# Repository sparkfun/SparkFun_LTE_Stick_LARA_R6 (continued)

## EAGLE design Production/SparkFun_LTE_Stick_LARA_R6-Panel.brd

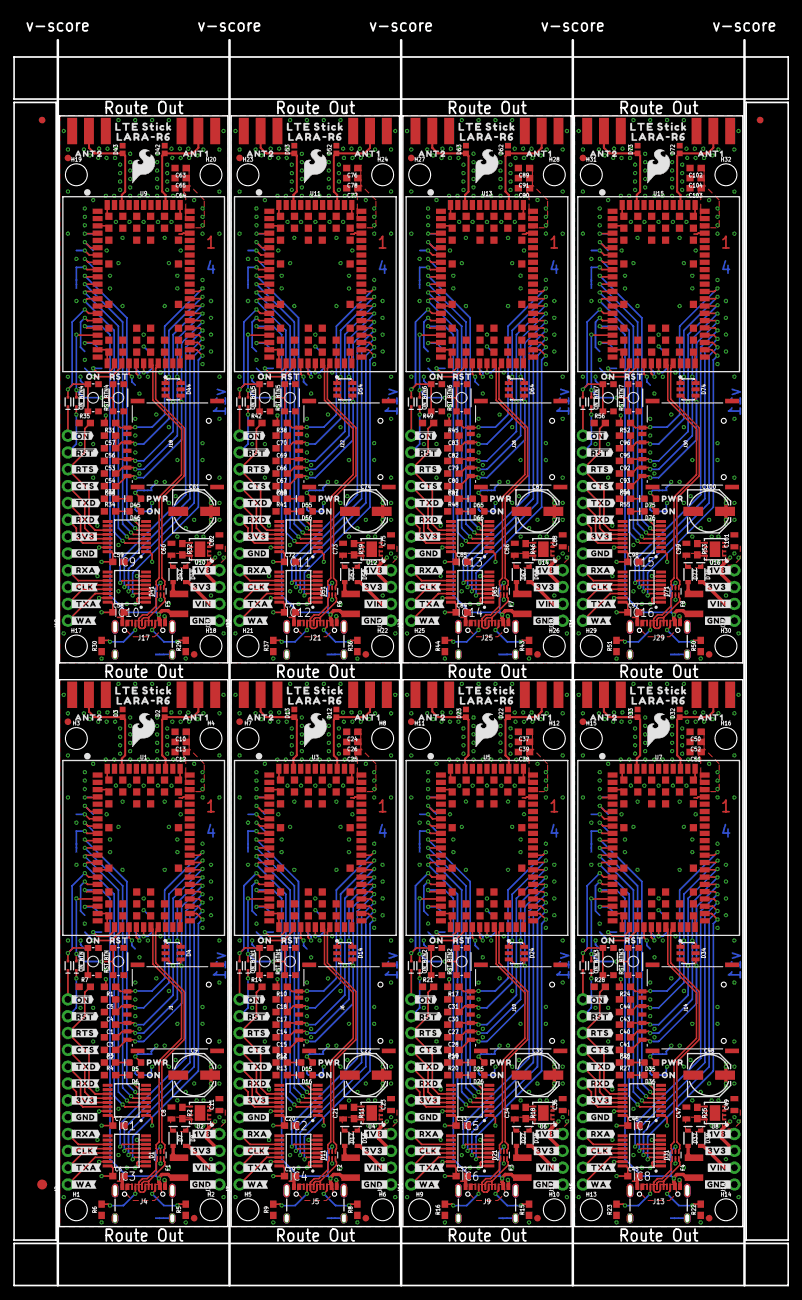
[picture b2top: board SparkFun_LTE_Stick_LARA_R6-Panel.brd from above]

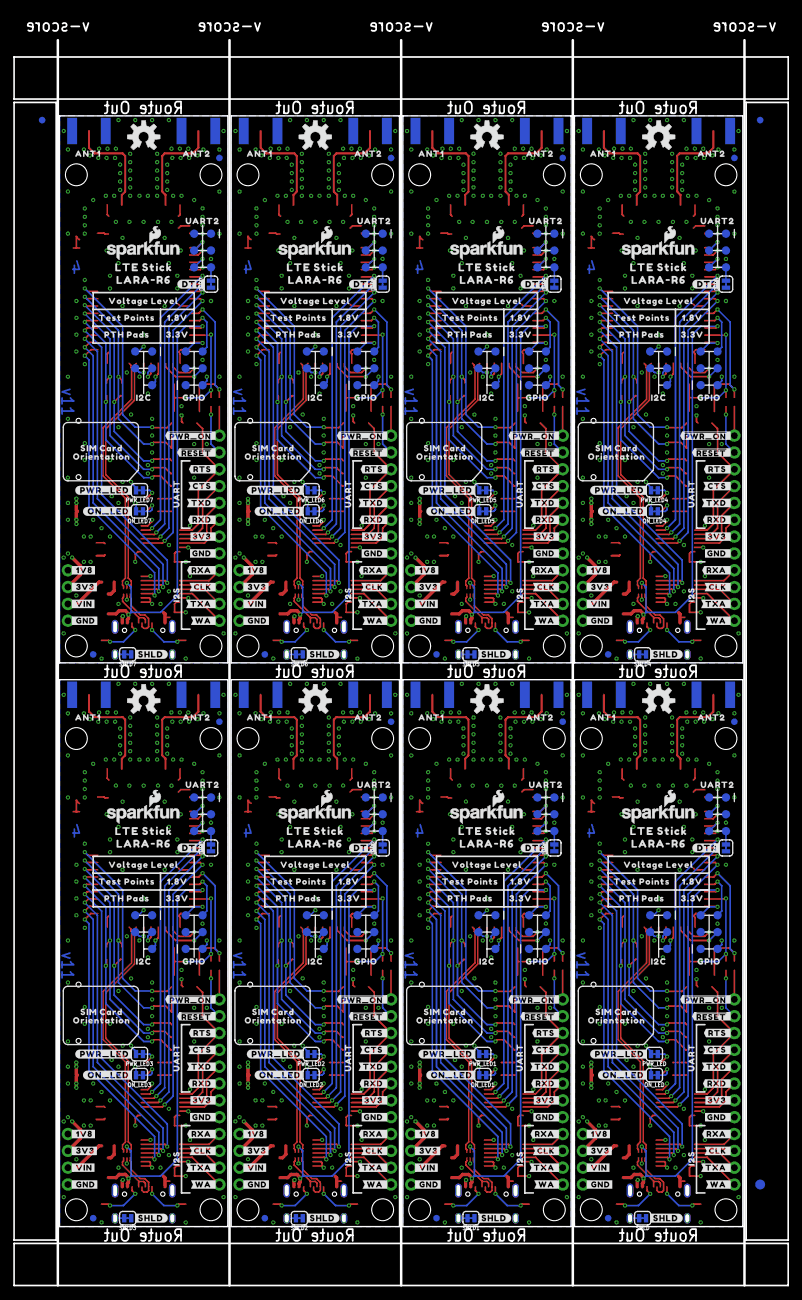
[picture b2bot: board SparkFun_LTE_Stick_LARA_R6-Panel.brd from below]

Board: 4 copper layers, 116.8 x 188.0 mm, 1086 parts (491 on the bottom side), 456 nets.

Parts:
C1, C2, C3, C4, C14, C15, C16, C17, C27, C28, C29, C30, C40, C41, C42, C43, C53, C54, C55, C56, C66, C67, C68, C69, C79, C80, C81, C82, C92, C93, C94, C95: 47pF; 0603
C5, C6, C7, C10, C18, C19, C20, C24, C31, C32, C33, C37, C44, C45, C46, C50, C57, C58, C59, C63, C70, C71, C72, C76, C83, C84, C85, C89, C96, C97, C98, C102: 0.1uF; 0603
C8, C11, C21, C23, C34, C36, C47, C49, C60, C62, C73, C75, C86, C88, C99, C101: 10uF; 0805
C9, C22, C35, C48, C61, C74, C87, C100: 100uF; PANASONIC_D
C12, C25, C38, C51, C64, C77, C90, C103: 15pF; 0603
C13, C26, C39, C52, C65, C78, C91, C104: 68pF; 0603
D1, D11, D21, D31, D41, D51, D61, D71: PRTR5V0U2F; SOT886
D2, D3, D12, D13, D22, D23, D32, D33, D42, D43, D52, D53, D62, D63, D72, D73: PESD0402-0402; 0402
D4, D14, D24, D34, D44, D54, D64, D74: DT1042-04SO-7; SOT23-6L
D5, D6, D15, D16, D25, D26, D35, D36, D45, D46, D55, D56, D65, D66, D75, D76: Red; LED-0603
D7, D8, D17, D18, D27, D28, D37, D38, D47, D48, D57, D58, D67, D68, D77, D78: 3A/10V/280mV; SOD-323
D9, D10, D19, D20, D29, D30, D39, D40, D49, D50, D59, D60, D69, D70, D79, D80: 120mA/40V/370mV; SOD-523
DTR, DTR1, DTR2, DTR3, DTR4, DTR5, DTR6, DTR7: JUMPER-SMT_2_NC_TRACE_SILK; SMT-JUMPER_2_NC_TRACE_SILK
E1, E2, E3, E4, E5, E6, E7, E8, E9, E10, E11, E12, E13, E14, E15, E16: ANTENNA-SMA-GROUNDEDEDGE_SMA; SMA-EDGE
E$1, E$2, E$3, E$4: FIDUCIAL-1X2
E$5, E$6: FIDUCIAL-1.5X3
F1, F2, F3, F4, F5, F6, F7, F8: 6V/2A; 1210
FD1, FD2, FD3, FD4, FD5, FD6, FD7, FD8, FD9, FD10, FD11, FD12, FD13, FD14, FD15, FD16, FD17, FD18, FD19, FD20, FD21, FD22, FD23, FD24, FD25, FD26, FD27, FD28, FD29, FD30, FD31, FD32: FIDUCIAL1X2; FIDUCIAL-1X2
H1, H2, H3, H4, H5, H6, H7, H8, H9, H10, H11, H12, H13, H14, H15, H16, H17, H18, H19, H20, H21, H22, H23, H24, H25, H26, H27, H28, H29, H30, H31, H32: STAND-OFF
IC1, IC2, IC3, IC4, IC5, IC6, IC7, IC8, IC9, IC10, IC11, IC12, IC13, IC14, IC15, IC16: SN74AVC4T774PW; SOP65P640X120-16N
J1, J6, J10, J14, J18, J22, J26, J30: NANO_SIM; NANO_SIM_PP
J2, J7, J11, J15, J19, J23, J27, J31: 1X12_NO_SILK
J3, J8, J12, J16, J20, J24, J28, J32: 1X04_NO_SILK
J4, J5, J9, J13, J17, J21, J25, J29: USB-C-16P_4LAYER-PADS
LOGO1, LOGO3, LOGO5, LOGO7, LOGO9, LOGO11, LOGO13, LOGO15: SFE_LOGO_NAME_FLAME.1_INCH; SFE_LOGO_NAME_FLAME_.1
LOGO2, LOGO4, LOGO6, LOGO8, LOGO10, LOGO12, LOGO14, LOGO16: OSHW-LOGOM; OSHW-LOGO-M
ON_BTN, ON_BTN1, ON_BTN2, ON_BTN3, ON_BTN4, ON_BTN5, ON_BTN6, ON_BTN7: MOMENTARY-SWITCH-SPST-SMD-4.6X2.8MM; TACTILE_SWITCH_SMD_4.6X2.8MM
ON_LED, ON_LED1, ON_LED2, ON_LED3, ON_LED4, ON_LED5, ON_LED6, ON_LED7: JUMPER-SMT_2_NC_TRACE_SILK; SMT-JUMPER_2_NC_TRACE_SILK
PWR_LED, PWR_LED1, PWR_LED2, PWR_LED3, PWR_LED4, PWR_LED5, PWR_LED6, PWR_LED7: JUMPER-SMT_2_NC_TRACE_SILK; SMT-JUMPER_2_NC_TRACE_SILK
R1, R2, R7, R10, R11, R14, R17, R18, R21, R24, R25, R28, R31, R32, R35, R38, R39, R42, R45, R46, R49, R52, R53, R56: 100k; 0603
R3, R12, R19, R26, R33, R40, R47, R54: 4.7k; 0603
R4, R13, R20, R27, R34, R41, R48, R55: 220; 0603
R5, R6, R8, R9, R15, R16, R22, R23, R29, R30, R36, R37, R43, R44, R50, R51: 5.1k; 0603
RST_BTN, RST_BTN1, RST_BTN2, RST_BTN3, RST_BTN4, RST_BTN5, RST_BTN6, RST_BTN7: MOMENTARY-SWITCH-SPST-SMD-4.6X2.8MM; TACTILE_SWITCH_SMD_4.6X2.8MM
SHLD, SHLD1, SHLD2, SHLD3, SHLD4, SHLD5, SHLD6, SHLD7: JUMPER-SMT_2_NC_TRACE_SILK; SMT-JUMPER_2_NC_TRACE_SILK
TP1, TP2, TP3, TP4, TP5, TP6, TP7, TP8, TP9, TP10, TP11, TP12, TP13, TP14, TP15, TP16, TP17, TP18, TP19, TP20, TP21, TP22, TP23, TP24, TP25, TP26, TP27, TP28, TP29, TP30, TP31, TP32, TP33, TP34, TP35, TP36, TP37, TP38, TP39, TP40, TP41, TP42, TP43, TP44, TP45, TP46, TP47, TP48, TP49, TP50, TP51, TP52, TP53, TP54, TP55, TP56, TP57, TP58, TP59, TP60, TP61, TP62, TP63, TP64, TP65, TP66, TP67, TP68, TP69, TP70, TP71, TP72, TP73, TP74, TP75, TP76, TP77, TP78, TP79, TP80, TP81, TP82, TP83, TP84, TP85, TP86, TP87, TP88, TP89, TP90, TP91, TP92, TP93, TP94, TP95, TP96, TP97, TP98, TP99, TP100, TP101, TP102, TP103, TP104, TP105, TP106, TP107, TP108, TP109, TP110, TP111, TP112, TP113, TP114, TP115, TP116, TP117, TP118, TP119, TP120, TP121, TP122, TP123, TP124, TP125, TP126, TP127, TP128, TP129, TP130, TP131, TP132, TP133, TP134, TP135, TP136: TEST-POINT3X5; PAD.03X.05
U1, U3, U5, U7, U9, U11, U13, U15: LARA-R6401; LARA-LGA
U2, U4, U6, U8, U10, U12, U14, U16: AP7361C-33; UDFN-8
U$1, U$25, U$55, U$79, U$123, U$140, U$184, U$201, U$245, U$262, U$306, U$323, U$367, U$384, U$428, U$445: LTE_STICK0
U$2, U$84, U$145, U$206, U$267, U$328, U$389, U$450: SFE_LOGO_FLAME_.2
U$3, U$15, U$63, U$73, U$124, U$134, U$185, U$195, U$246, U$256, U$307, U$317, U$368, U$378, U$429, U$439: #_3V3#0
U$4, U$5, U$64, U$65, U$125, U$126, U$186, U$187, U$247, U$248, U$308, U$309, U$369, U$370, U$430, U$431: #_GND#0
U$6, U$80, U$141, U$202, U$263, U$324, U$385, U$446: #SHLD#0
U$7, U$8, U$66, U$67, U$127, U$128, U$188, U$189, U$249, U$250, U$310, U$311, U$371, U$372, U$432, U$433: #GND_#0
U$9, U$12, U$68, U$70, U$129, U$131, U$190, U$192, U$251, U$253, U$312, U$314, U$373, U$375, U$434, U$436: #3V3_#0
U$10, U$81, U$142, U$203, U$264, U$325, U$386, U$447: #DTR#0
U$11, U$69, U$130, U$191, U$252, U$313, U$374, U$435: #VIN_#0
U$13, U$71, U$132, U$193, U$254, U$315, U$376, U$437: #1V8_#0
U$14, U$72, U$133, U$194, U$255, U$316, U$377, U$438: #_1V8#0
U$16, U$74, U$135, U$196, U$257, U$318, U$379, U$440: #_VIN#0
U$17, U$75, U$136, U$197, U$258, U$319, U$380, U$441: #_CTS#0
U$18, U$76, U$137, U$198, U$259, U$320, U$381, U$442: #_RTS#0
U$19, U$95, U$156, U$217, U$278, U$339, U$400, U$461: #RXD_#0
U$20, U$96, U$157, U$218, U$279, U$340, U$401, U$462: #TXD_#0
U$21, U$77, U$138, U$199, U$260, U$321, U$382, U$443: #_CLK#0
U$22, U$78, U$139, U$200, U$261, U$322, U$383, U$444: #_WA#0
U$23, U$97, U$158, U$219, U$280, U$341, U$402, U$463: #RXA_#0
U$24, U$98, U$159, U$220, U$281, U$342, U$403, U$464: #TXA_#0
U$26, U$105, U$166, U$227, U$288, U$349, U$410, U$471: SIM_CARD0
U$27, U$106, U$167, U$228, U$289, U$350, U$411, U$472: VOLTAGE_LEVEL0
U$28, U$82, U$143, U$204, U$265, U$326, U$387, U$448: PWR0
U$29, U$36, U$119, U$120, U$180, U$181, U$241, U$242, U$302, U$303, U$363, U$364, U$424, U$425, U$485, U$486: ANT10
U$30, U$107, U$168, U$229, U$290, U$351, U$412, U$473: TEST_POINTS0
U$31, U$35, U$85, U$86, U$146, U$147, U$207, U$208, U$268, U$269, U$329, U$330, U$390, U$391, U$451, U$452: LARA#R60
U$32, U$91, U$152, U$213, U$274, U$335, U$396, U$457: #_RXA#0
U$33, U$83, U$144, U$205, U$266, U$327, U$388, U$449: #_#RST##0
U$34, U$108, U$169, U$230, U$291, U$352, U$413, U$474: PTH_PADS0
U$37, U$39, U$115, U$116, U$176, U$177, U$237, U$238, U$298, U$299, U$359, U$360, U$420, U$421, U$481, U$482: ON0
U$38, U$90, U$151, U$212, U$273, U$334, U$395, U$456: ##PWR_ON#_#0
U$40, U$92, U$153, U$214, U$275, U$336, U$397, U$458: #_TXA#0
U$41, U$93, U$154, U$215, U$276, U$337, U$398, U$459: #_TXD#0
U$42, U$94, U$155, U$216, U$277, U$338, U$399, U$460: #_RXD#0
U$43, U$99, U$160, U$221, U$282, U$343, U$404, U$465: #CLK_#0
U$44, U$100, U$161, U$222, U$283, U$344, U$405, U$466: #WA_#0
U$45, U$87, U$148, U$209, U$270, U$331, U$392, U$453: #RTS_#0
U$46, U$88, U$149, U$210, U$271, U$332, U$393, U$454: #CTS_#0
U$47, U$89, U$150, U$211, U$272, U$333, U$394, U$455: ##RESET#_#0
U$48, U$101, U$162, U$223, U$284, U$345, U$406, U$467: UART0
U$49, U$102, U$163, U$224, U$285, U$346, U$407, U$468: I2S0
U$50, U$109, U$170, U$231, U$292, U$353, U$414, U$475: 1#8V0
U$51, U$103, U$164, U$225, U$286, U$347, U$408, U$469: ORIENTATION0
U$52, U$104, U$165, U$226, U$287, U$348, U$409, U$470: RST0
U$53, U$117, U$178, U$239, U$300, U$361, U$422, U$483: #ON_LED#0
U$54, U$110, U$171, U$232, U$293, U$354, U$415, U$476: 3#3V0
U$56, U$111, U$172, U$233, U$294, U$355, U$416, U$477: UART20
U$57, U$112, U$173, U$234, U$295, U$356, U$417, U$478: GPIO0
U$58, U$113, U$174, U$235, U$296, U$357, U$418, U$479: I2C0
U$59, U$114, U$175, U$236, U$297, U$358, U$419, U$480: #_#ON##0
U$60, U$118, U$179, U$240, U$301, U$362, U$423, U$484: #PWR_LED#0
U$61, U$62, U$121, U$122, U$182, U$183, U$243, U$244, U$304, U$305, U$365, U$366, U$426, U$427, U$487, U$488: ANT20

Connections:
1.8V: C6.1, C7.1, IC1.1, IC1.7, IC1.16, IC3.1, IC3.2, IC3.7, IC3.16, J3.4, ON_LED.2, R1.2, TP3.1, TP9.1, TP15.1, U1.4
1.8V1: C19.1, C20.1, IC2.1, IC2.7, IC2.16, IC4.1, IC4.2, IC4.7, IC4.16, J8.4, ON_LED1.2, R10.2, TP20.1, TP26.1, TP32.1, U3.4
1.8V2: C32.1, C33.1, IC5.1, IC5.7, IC5.16, IC6.1, IC6.2, IC6.7, IC6.16, J12.4, ON_LED2.2, R17.2, TP37.1, TP43.1, TP49.1, U5.4
1.8V3: C45.1, C46.1, IC7.1, IC7.7, IC7.16, IC8.1, IC8.2, IC8.7, IC8.16, J16.4, ON_LED3.2, R24.2, TP54.1, TP60.1, TP66.1, U7.4
1.8V4: C58.1, C59.1, IC9.1, IC9.7, IC9.16, IC10.1, IC10.2, IC10.7, IC10.16, J20.4, ON_LED4.2, R31.2, TP71.1, TP77.1, TP83.1, U9.4
1.8V5: C71.1, C72.1, IC11.1, IC11.7, IC11.16, IC12.1, IC12.2, IC12.7, IC12.16, J24.4, ON_LED5.2, R38.2, TP88.1, TP94.1, TP100.1, U11.4
1.8V6: C84.1, C85.1, IC13.1, IC13.7, IC13.16, IC14.1, IC14.2, IC14.7, IC14.16, J28.4, ON_LED6.2, R45.2, TP105.1, TP111.1, TP117.1, U13.4
1.8V7: C97.1, C98.1, IC15.1, IC15.7, IC15.16, IC16.1, IC16.2, IC16.7, IC16.16, J32.4, ON_LED7.2, R52.2, TP122.1, TP128.1, TP134.1, U15.4
3.3V: C9.+, C10.1, C11.1, C12.1, C13.1, IC1.15, IC3.15, J2.6, J3.3, PWR_LED.2, U1.51, U1.52, U1.53, U2.1
3.3V1: C22.+, C23.1, C24.1, C25.1, C26.1, IC2.15, IC4.15, J7.6, J8.3, PWR_LED1.2, U3.51, U3.52, U3.53, U4.1
3.3V2: C35.+, C36.1, C37.1, C38.1, C39.1, IC5.15, IC6.15, J11.6, J12.3, PWR_LED2.2, U5.51, U5.52, U5.53, U6.1
3.3V3: C48.+, C49.1, C50.1, C51.1, C52.1, IC7.15, IC8.15, J15.6, J16.3, PWR_LED3.2, U7.51, U7.52, U7.53, U8.1
3.3V4: C61.+, C62.1, C63.1, C64.1, C65.1, IC9.15, IC10.15, J19.6, J20.3, PWR_LED4.2, U9.51, U9.52, U9.53, U10.1
3.3V5: C74.+, C75.1, C76.1, C77.1, C78.1, IC11.15, IC12.15, J23.6, J24.3, PWR_LED5.2, U11.51, U11.52, U11.53, U12.1
3.3V6: C87.+, C88.1, C89.1, C90.1, C91.1, IC13.15, IC14.15, J27.6, J28.3, PWR_LED6.2, U13.51, U13.52, U13.53, U14.1
3.3V7: C100.+, C101.1, C102.1, C103.1, C104.1, IC15.15, IC16.15, J31.6, J32.3, PWR_LED7.2, U15.51, U15.52, U15.53, U16.1
5V: D7.A, F1.2
5V1: D17.A, F2.2
5V2: D27.A, F3.2
5V3: D37.A, F4.2
5V4: D47.A, F5.2
5V5: D57.A, F6.2
5V6: D67.A, F7.2
5V7: D77.A, F8.2
!PWR_ON!: D9.A, ON_BTN.3, ON_BTN.4, U1.15
!PWR_ON!1: D19.A, ON_BTN1.3, ON_BTN1.4, U3.15
!PWR_ON!2: D29.A, ON_BTN2.3, ON_BTN2.4, U5.15
!PWR_ON!3: D39.A, ON_BTN3.3, ON_BTN3.4, U7.15
!PWR_ON!4: D49.A, ON_BTN4.3, ON_BTN4.4, U9.15
!PWR_ON!5: D59.A, ON_BTN5.3, ON_BTN5.4, U11.15
!PWR_ON!6: D69.A, ON_BTN6.3, ON_BTN6.4, U13.15
!PWR_ON!7: D79.A, ON_BTN7.3, ON_BTN7.4, U15.15
!RESET!: D10.A, RST_BTN.3, RST_BTN.4, U1.18
!RESET!1: D20.A, RST_BTN1.3, RST_BTN1.4, U3.18
!RESET!2: D30.A, RST_BTN2.3, RST_BTN2.4, U5.18
!RESET!3: D40.A, RST_BTN3.3, RST_BTN3.4, U7.18
!RESET!4: D50.A, RST_BTN4.3, RST_BTN4.4, U9.18
!RESET!5: D60.A, RST_BTN5.3, RST_BTN5.4, U11.18
!RESET!6: D70.A, RST_BTN6.3, RST_BTN6.4, U13.18
!RESET!7: D80.A, RST_BTN7.3, RST_BTN7.4, U15.18
ANT1: D2.1, E2.SIG, U1.56
ANT2: D3.1, E1.SIG, U1.62
ANT3: D12.1, E4.SIG, U3.56
ANT4: D13.1, E3.SIG, U3.62
ANT5: D22.1, E6.SIG, U5.56
ANT6: D23.1, E5.SIG, U5.62
ANT7: D32.1, E8.SIG, U7.56
ANT8: D33.1, E7.SIG, U7.62
ANT9: D42.1, E10.SIG, U9.56
ANT10: D43.1, E9.SIG, U9.62
ANT11: D52.1, E12.SIG, U11.56
ANT12: D53.1, E11.SIG, U11.62
ANT13: D62.1, E14.SIG, U13.56
ANT14: D63.1, E13.SIG, U13.62
ANT15: D72.1, E16.SIG, U15.56
ANT16: D73.1, E15.SIG, U15.62
CTS_1: IC2.5, U3.11
CTS_2: IC2.12, J7.9
CTS_3: IC5.5, U5.11
CTS_4: IC5.12, J11.9
CTS_5: IC7.5, U7.11
CTS_6: IC7.12, J15.9
CTS_7: IC9.5, U9.11
CTS_8: IC9.12, J19.9
CTS_9: IC11.5, U11.11
CTS_10: IC11.12, J23.9
CTS_11: IC13.5, U13.11
CTS_12: IC13.12, J27.9
CTS_13: IC15.5, U15.11
CTS_14: IC15.12, J31.9
CTS_18: IC1.5, U1.11
CTS_33: IC1.12, J2.9
DCD/RXD2_1: TP24.1, U3.8
DCD/RXD2_2: TP41.1, U5.8
DCD/RXD2_3: TP58.1, U7.8
DCD/RXD2_4: TP75.1, U9.8
DCD/RXD2_5: TP92.1, U11.8
DCD/RXD2_6: TP109.1, U13.8
DCD/RXD2_7: TP126.1, U15.8
DCD/RXD2_18: TP7.1, U1.8
DSR/RTS2_1: TP22.1, U3.6
DSR/RTS2_2: TP39.1, U5.6
DSR/RTS2_3: TP56.1, U7.6
DSR/RTS2_4: TP73.1, U9.6
DSR/RTS2_5: TP90.1, U11.6
DSR/RTS2_6: TP107.1, U13.6
DSR/RTS2_7: TP124.1, U15.6
DSR/RTS2_18: TP5.1, U1.6
DTR/TXD2_1: DTR1.2, TP25.1, U3.9
DTR/TXD2_2: DTR2.2, TP42.1, U5.9
DTR/TXD2_3: DTR3.2, TP59.1, U7.9
DTR/TXD2_4: DTR4.2, TP76.1, U9.9
DTR/TXD2_5: DTR5.2, TP93.1, U11.9
DTR/TXD2_6: DTR6.2, TP110.1, U13.9
DTR/TXD2_7: DTR7.2, TP127.1, U15.9
DTR/TXD2_18: DTR.2, TP8.1, U1.9
EN: R2.1, U2.5
EN1: R11.1, U4.5
EN2: R18.1, U6.5
EN3: R25.1, U8.5
EN4: R32.1, U10.5
EN5: R39.1, U12.5
EN6: R46.1, U14.5
EN7: R53.1, U16.5
GND: C1.2, C2.2, C3.2, C4.2, C5.2, C6.2, C7.2, C8.2, C9.-, C10.2, C11.2, C12.2, C13.2, D1.2, D2.2, D3.2, D4.2, D4.5, DTR.1, E1.GND@0, E1.GND@1, E1.GND@2, E1.GND@3, E2.GND@0, E2.GND@1, E2.GND@2, E2.GND@3, IC1.2, IC1.8, IC1.9, IC1.10, IC3.8, IC3.9, IC3.10, J1.A1, J1.A2, J1.A3, J1.A4, J1.C5, J2.5, J3.1, J4.GND, J4.GND2, ON_BTN.1, ON_BTN.2, R3.1, R4.1, R5.1, R6.1, R7.1, RST_BTN.1, RST_BTN.2, SHLD.1, TP4.1, TP10.1, TP16.1, U1.1, U1.3, U1.5, U1.14, U1.20, U1.21, U1.22, U1.30, U1.32, U1.43, U1.50, U1.54, U1.55, U1.57, U1.58, U1.60, U1.61, U1.63, U1.64, U1.65, U1.66, U1.67, U1.68, U1.69, U1.70, U1.71, U1.72, U1.73, U1.74, U1.75, U1.76, U1.77, U1.78, U1.79, U1.80, U1.81, U1.82, U1.83, U1.84, U1.85, U1.86, U1.87, U1.88, U1.89, U1.90, U1.91, U1.92, U1.93, U1.94, U1.95, U1.96, U2.4, U2.EP
GND1: C14.2, C15.2, C16.2, C17.2, C18.2, C19.2, C20.2, C21.2, C22.-, C23.2, C24.2, C25.2, C26.2, D11.2, D12.2, D13.2, D14.2, D14.5, DTR1.1, E3.GND@0, E3.GND@1, E3.GND@2, E3.GND@3, E4.GND@0, E4.GND@1, E4.GND@2, E4.GND@3, IC2.2, IC2.8, IC2.9, IC2.10, IC4.8, IC4.9, IC4.10, J5.GND, J5.GND2, J6.A1, J6.A2, J6.A3, J6.A4, J6.C5, J7.5, J8.1, ON_BTN1.1, ON_BTN1.2, R8.1, R9.1, R12.1, R13.1, R14.1, RST_BTN1.1, RST_BTN1.2, SHLD1.1, TP21.1, TP27.1, TP33.1, U3.1, U3.3, U3.5, U3.14, U3.20, U3.21, U3.22, U3.30, U3.32, U3.43, U3.50, U3.54, U3.55, U3.57, U3.58, U3.60, U3.61, U3.63, U3.64, U3.65, U3.66, U3.67, U3.68, U3.69, U3.70, U3.71, U3.72, U3.73, U3.74, U3.75, U3.76, U3.77, U3.78, U3.79, U3.80, U3.81, U3.82, U3.83, U3.84, U3.85, U3.86, U3.87, U3.88, U3.89, U3.90, U3.91, U3.92, U3.93, U3.94, U3.95, U3.96, U4.4, U4.EP
GND2: C27.2, C28.2, C29.2, C30.2, C31.2, C32.2, C33.2, C34.2, C35.-, C36.2, C37.2, C38.2, C39.2, D21.2, D22.2, D23.2, D24.2, D24.5, DTR2.1, E5.GND@0, E5.GND@1, E5.GND@2, E5.GND@3, E6.GND@0, E6.GND@1, E6.GND@2, E6.GND@3, IC5.2, IC5.8, IC5.9, IC5.10, IC6.8, IC6.9, IC6.10, J9.GND, J9.GND2, J10.A1, J10.A2, J10.A3, J10.A4, J10.C5, J11.5, J12.1, ON_BTN2.1, ON_BTN2.2, R15.1, R16.1, R19.1, R20.1, R21.1, RST_BTN2.1, RST_BTN2.2, SHLD2.1, TP38.1, TP44.1, TP50.1, U5.1, U5.3, U5.5, U5.14, U5.20, U5.21, U5.22, U5.30, U5.32, U5.43, U5.50, U5.54, U5.55, U5.57, U5.58, U5.60, U5.61, U5.63, U5.64, U5.65, U5.66, U5.67, U5.68, U5.69, U5.70, U5.71, U5.72, U5.73, U5.74, U5.75, U5.76, U5.77, U5.78, U5.79, U5.80, U5.81, U5.82, U5.83, U5.84, U5.85, U5.86, U5.87, U5.88, U5.89, U5.90, U5.91, U5.92, U5.93, U5.94, U5.95, U5.96, U6.4, U6.EP
GND3: C40.2, C41.2, C42.2, C43.2, C44.2, C45.2, C46.2, C47.2, C48.-, C49.2, C50.2, C51.2, C52.2, D31.2, D32.2, D33.2, D34.2, D34.5, DTR3.1, E7.GND@0, E7.GND@1, E7.GND@2, E7.GND@3, E8.GND@0, E8.GND@1, E8.GND@2, E8.GND@3, IC7.2, IC7.8, IC7.9, IC7.10, IC8.8, IC8.9, IC8.10, J13.GND, J13.GND2, J14.A1, J14.A2, J14.A3, J14.A4, J14.C5, J15.5, J16.1, ON_BTN3.1, ON_BTN3.2, R22.1, R23.1, R26.1, R27.1, R28.1, RST_BTN3.1, RST_BTN3.2, SHLD3.1, TP55.1, TP61.1, TP67.1, U7.1, U7.3, U7.5, U7.14, U7.20, U7.21, U7.22, U7.30, U7.32, U7.43, U7.50, U7.54, U7.55, U7.57, U7.58, U7.60, U7.61, U7.63, U7.64, U7.65, U7.66, U7.67, U7.68, U7.69, U7.70, U7.71, U7.72, U7.73, U7.74, U7.75, U7.76, U7.77, U7.78, U7.79, U7.80, U7.81, U7.82, U7.83, U7.84, U7.85, U7.86, U7.87, U7.88, U7.89, U7.90, U7.91, U7.92, U7.93, U7.94, U7.95, U7.96, U8.4, U8.EP
GND4: C53.2, C54.2, C55.2, C56.2, C57.2, C58.2, C59.2, C60.2, C61.-, C62.2, C63.2, C64.2, C65.2, D41.2, D42.2, D43.2, D44.2, D44.5, DTR4.1, E9.GND@0, E9.GND@1, E9.GND@2, E9.GND@3, E10.GND@0, E10.GND@1, E10.GND@2, E10.GND@3, IC9.2, IC9.8, IC9.9, IC9.10, IC10.8, IC10.9, IC10.10, J17.GND, J17.GND2, J18.A1, J18.A2, J18.A3, J18.A4, J18.C5, J19.5, J20.1, ON_BTN4.1, ON_BTN4.2, R29.1, R30.1, R33.1, R34.1, R35.1, RST_BTN4.1, RST_BTN4.2, SHLD4.1, TP72.1, TP78.1, TP84.1, U9.1, U9.3, U9.5, U9.14, U9.20, U9.21, U9.22, U9.30, U9.32, U9.43, U9.50, U9.54, U9.55, U9.57, U9.58, U9.60, U9.61, U9.63, U9.64, U9.65, U9.66, U9.67, U9.68, U9.69, U9.70, U9.71, U9.72, U9.73, U9.74, U9.75, U9.76, U9.77, U9.78, U9.79, U9.80, U9.81, U9.82, U9.83, U9.84, U9.85, U9.86, U9.87, U9.88, U9.89, U9.90, U9.91, U9.92, U9.93, U9.94, U9.95, U9.96, U10.4, U10.EP
GND5: C66.2, C67.2, C68.2, C69.2, C70.2, C71.2, C72.2, C73.2, C74.-, C75.2, C76.2, C77.2, C78.2, D51.2, D52.2, D53.2, D54.2, D54.5, DTR5.1, E11.GND@0, E11.GND@1, E11.GND@2, E11.GND@3, E12.GND@0, E12.GND@1, E12.GND@2, E12.GND@3, IC11.2, IC11.8, IC11.9, IC11.10, IC12.8, IC12.9, IC12.10, J21.GND, J21.GND2, J22.A1, J22.A2, J22.A3, J22.A4, J22.C5, J23.5, J24.1, ON_BTN5.1, ON_BTN5.2, R36.1, R37.1, R40.1, R41.1, R42.1, RST_BTN5.1, RST_BTN5.2, SHLD5.1, TP89.1, TP95.1, TP101.1, U11.1, U11.3, U11.5, U11.14, U11.20, U11.21, U11.22, U11.30, U11.32, U11.43, U11.50, U11.54, U11.55, U11.57, U11.58, U11.60, U11.61, U11.63, U11.64, U11.65, U11.66, U11.67, U11.68, U11.69, U11.70, U11.71, U11.72, U11.73, U11.74, U11.75, U11.76, U11.77, U11.78, U11.79, U11.80, U11.81, U11.82, U11.83, U11.84, U11.85, U11.86, U11.87, U11.88, U11.89, U11.90, U11.91, U11.92, U11.93, U11.94, U11.95, U11.96, U12.4, U12.EP
GND6: C79.2, C80.2, C81.2, C82.2, C83.2, C84.2, C85.2, C86.2, C87.-, C88.2, C89.2, C90.2, C91.2, D61.2, D62.2, D63.2, D64.2, D64.5, DTR6.1, E13.GND@0, E13.GND@1, E13.GND@2, E13.GND@3, E14.GND@0, E14.GND@1, E14.GND@2, E14.GND@3, IC13.2, IC13.8, IC13.9, IC13.10, IC14.8, IC14.9, IC14.10, J25.GND, J25.GND2, J26.A1, J26.A2, J26.A3, J26.A4, J26.C5, J27.5, J28.1, ON_BTN6.1, ON_BTN6.2, R43.1, R44.1, R47.1, R48.1, R49.1, RST_BTN6.1, RST_BTN6.2, SHLD6.1, TP106.1, TP112.1, TP118.1, U13.1, U13.3, U13.5, U13.14, U13.20, U13.21, U13.22, U13.30, U13.32, U13.43, U13.50, U13.54, U13.55, U13.57, U13.58, U13.60, U13.61, U13.63, U13.64, U13.65, U13.66, U13.67, U13.68, U13.69, U13.70, U13.71, U13.72, U13.73, U13.74, U13.75, U13.76, U13.77, U13.78, U13.79, U13.80, U13.81, U13.82, U13.83, U13.84, U13.85, U13.86, U13.87, U13.88, U13.89, U13.90, U13.91, U13.92, U13.93, U13.94, U13.95, U13.96, U14.4, U14.EP
GND7: C92.2, C93.2, C94.2, C95.2, C96.2, C97.2, C98.2, C99.2, C100.-, C101.2, C102.2, C103.2, C104.2, D71.2, D72.2, D73.2, D74.2, D74.5, DTR7.1, E15.GND@0, E15.GND@1, E15.GND@2, E15.GND@3, E16.GND@0, E16.GND@1, E16.GND@2, E16.GND@3, IC15.2, IC15.8, IC15.9, IC15.10, IC16.8, IC16.9, IC16.10, J29.GND, J29.GND2, J30.A1, J30.A2, J30.A3, J30.A4, J30.C5, J31.5, J32.1, ON_BTN7.1, ON_BTN7.2, R50.1, R51.1, R54.1, R55.1, R56.1, RST_BTN7.1, RST_BTN7.2, SHLD7.1, TP123.1, TP129.1, TP135.1, U15.1, U15.3, U15.5, U15.14, U15.20, U15.21, U15.22, U15.30, U15.32, U15.43, U15.50, U15.54, U15.55, U15.57, U15.58, U15.60, U15.61, U15.63, U15.64, U15.65, U15.66, U15.67, U15.68, U15.69, U15.70, U15.71, U15.72, U15.73, U15.74, U15.75, U15.76, U15.77, U15.78, U15.79, U15.80, U15.81, U15.82, U15.83, U15.84, U15.85, U15.86, U15.87, U15.88, U15.89, U15.90, U15.91, U15.92, U15.93, U15.94, U15.95, U15.96, U16.4, U16.EP
I2S_CLK_1: IC4.12, J7.3
I2S_CLK_2: IC4.5, U3.36
I2S_CLK_3: IC6.12, J11.3
I2S_CLK_4: IC6.5, U5.36
I2S_CLK_5: IC8.12, J15.3
I2S_CLK_6: IC8.5, U7.36
I2S_CLK_7: IC10.12, J19.3
I2S_CLK_8: IC10.5, U9.36
I2S_CLK_9: IC12.12, J23.3
I2S_CLK_10: IC12.5, U11.36
I2S_CLK_11: IC14.12, J27.3
I2S_CLK_12: IC14.5, U13.36
I2S_CLK_13: IC16.12, J31.3
I2S_CLK_14: IC16.5, U15.36
I2S_CLK_18: IC3.5, U1.36
I2S_CLK_33: IC3.12, J2.3
I2S_RXA_1: IC4.11, J7.4
I2S_RXA_2: IC4.6, U3.37
I2S_RXA_3: IC6.11, J11.4
I2S_RXA_4: IC6.6, U5.37
I2S_RXA_5: IC8.11, J15.4
I2S_RXA_6: IC8.6, U7.37
I2S_RXA_7: IC10.11, J19.4
I2S_RXA_8: IC10.6, U9.37
I2S_RXA_9: IC12.11, J23.4
I2S_RXA_10: IC12.6, U11.37
I2S_RXA_11: IC14.11, J27.4
I2S_RXA_12: IC14.6, U13.37
I2S_RXA_13: IC16.11, J31.4
I2S_RXA_14: IC16.6, U15.37
I2S_RXA_18: IC3.6, U1.37
I2S_RXA_33: IC3.11, J2.4
I2S_TXA_1: IC4.13, J7.2
I2S_TXA_2: IC4.4, U3.35
I2S_TXA_3: IC6.13, J11.2
I2S_TXA_4: IC6.4, U5.35
I2S_TXA_5: IC8.13, J15.2
I2S_TXA_6: IC8.4, U7.35
I2S_TXA_7: IC10.13, J19.2
I2S_TXA_8: IC10.4, U9.35
I2S_TXA_9: IC12.13, J23.2
I2S_TXA_10: IC12.4, U11.35
I2S_TXA_11: IC14.13, J27.2
I2S_TXA_12: IC14.4, U13.35
I2S_TXA_13: IC16.13, J31.2
I2S_TXA_14: IC16.4, U15.35
I2S_TXA_18: IC3.4, U1.35
I2S_TXA_33: IC3.13, J2.2
I2S_WA_1: IC4.14, J7.1
I2S_WA_2: IC4.3, U3.34
I2S_WA_3: IC6.14, J11.1
I2S_WA_4: IC6.3, U5.34
I2S_WA_5: IC8.14, J15.1
I2S_WA_6: IC8.3, U7.34
I2S_WA_7: IC10.14, J19.1
I2S_WA_8: IC10.3, U9.34
I2S_WA_9: IC12.14, J23.1
I2S_WA_10: IC12.3, U11.34
I2S_WA_11: IC14.14, J27.1
I2S_WA_12: IC14.3, U13.34
I2S_WA_13: IC16.14, J31.1
I2S_WA_14: IC16.3, U15.34
I2S_WA_18: IC3.3, U1.34
I2S_WA_33: IC3.14, J2.1
IO1_1: TP28.1, U3.16
IO1_2: TP45.1, U5.16
IO1_3: TP62.1, U7.16
IO1_4: TP79.1, U9.16
IO1_5: TP96.1, U11.16
IO1_6: TP113.1, U13.16
IO1_7: TP130.1, U15.16
IO1_18: TP11.1, U1.16
IO2_1: TP29.1, U3.23
IO2_2: TP46.1, U5.23
IO2_3: TP63.1, U7.23
IO2_4: TP80.1, U9.23
IO2_5: TP97.1, U11.23
IO2_6: TP114.1, U13.23
IO2_7: TP131.1, U15.23
IO2_18: TP12.1, U1.23
IO3_1: TP30.1, U3.24
IO3_2: TP47.1, U5.24
IO3_3: TP64.1, U7.24
IO3_4: TP81.1, U9.24
IO3_5: TP98.1, U11.24
IO3_6: TP115.1, U13.24
IO3_7: TP132.1, U15.24
IO3_18: TP13.1, U1.24
IO4_1: TP34.1, U3.25
IO4_2: TP51.1, U5.25
IO4_3: TP68.1, U7.25
IO4_4: TP85.1, U9.25
IO4_5: TP102.1, U11.25
IO4_6: TP119.1, U13.25
IO4_7: TP136.1, U15.25
IO4_18: TP17.1, U1.25
IO6_1: TP31.1, U3.19
IO6_2: TP48.1, U5.19
IO6_3: TP65.1, U7.19
IO6_4: TP82.1, U9.19
IO6_5: TP99.1, U11.19
IO6_6: TP116.1, U13.19
IO6_7: TP133.1, U15.19
IO6_18: TP14.1, U1.19
unnamed: D5.C, R3.2
unnamed: D5.A, PWR_LED.1
unnamed: D6.A, ON_LED.1
unnamed: D6.C, R4.2
unnamed: D10.C, J2.11
unnamed: D9.C, J2.12
unnamed: C8.1, D7.C, D8.C, R2.2, U2.8
unnamed: J4.B5, R5.2
unnamed: J4.A5, R6.2
unnamed: D1.3, J4.A6, J4.B6
unnamed: D1.1, J4.A7, J4.B7
unnamed: J5.B5, R8.2
unnamed: J5.A5, R9.2
unnamed: D11.3, J5.A6, J5.B6
unnamed: D11.1, J5.A7, J5.B7
unnamed: D15.C, R12.2
unnamed: D15.A, PWR_LED1.1
unnamed: D16.A, ON_LED1.1
unnamed: D16.C, R13.2
unnamed: D20.C, J7.11
unnamed: D19.C, J7.12
unnamed: C21.1, D17.C, D18.C, R11.2, U4.8
unnamed: J9.B5, R15.2
unnamed: J9.A5, R16.2
unnamed: D21.3, J9.A6, J9.B6
unnamed: D21.1, J9.A7, J9.B7
unnamed: D25.C, R19.2
unnamed: D25.A, PWR_LED2.1
unnamed: D26.A, ON_LED2.1
unnamed: D26.C, R20.2
unnamed: D30.C, J11.11
unnamed: D29.C, J11.12
unnamed: C34.1, D27.C, D28.C, R18.2, U6.8
unnamed: J13.B5, R22.2
unnamed: J13.A5, R23.2
unnamed: D31.3, J13.A6, J13.B6
unnamed: D31.1, J13.A7, J13.B7
unnamed: D35.C, R26.2
unnamed: D35.A, PWR_LED3.1
unnamed: D36.A, ON_LED3.1
unnamed: D36.C, R27.2
unnamed: D40.C, J15.11
unnamed: D39.C, J15.12
unnamed: C47.1, D37.C, D38.C, R25.2, U8.8
unnamed: J17.B5, R29.2
unnamed: J17.A5, R30.2
unnamed: D41.3, J17.A6, J17.B6
unnamed: D41.1, J17.A7, J17.B7
unnamed: D45.C, R33.2
unnamed: D45.A, PWR_LED4.1
unnamed: D46.A, ON_LED4.1
unnamed: D46.C, R34.2
unnamed: D50.C, J19.11
unnamed: D49.C, J19.12
unnamed: C60.1, D47.C, D48.C, R32.2, U10.8
unnamed: J21.B5, R36.2
unnamed: J21.A5, R37.2
unnamed: D51.3, J21.A6, J21.B6
unnamed: D51.1, J21.A7, J21.B7
unnamed: D55.C, R40.2
unnamed: D55.A, PWR_LED5.1
unnamed: D56.A, ON_LED5.1
unnamed: D56.C, R41.2
unnamed: D60.C, J23.11
unnamed: D59.C, J23.12
unnamed: C73.1, D57.C, D58.C, R39.2, U12.8
unnamed: J25.B5, R43.2
unnamed: J25.A5, R44.2
unnamed: D61.3, J25.A6, J25.B6
unnamed: D61.1, J25.A7, J25.B7
unnamed: D65.C, R47.2
unnamed: D65.A, PWR_LED6.1
unnamed: D66.A, ON_LED6.1
unnamed: D66.C, R48.2
unnamed: D70.C, J27.11
unnamed: D69.C, J27.12
unnamed: C86.1, D67.C, D68.C, R46.2, U14.8
unnamed: J29.B5, R50.2
unnamed: J29.A5, R51.2
unnamed: D71.3, J29.A6, J29.B6
unnamed: D71.1, J29.A7, J29.B7
unnamed: D75.C, R54.2
unnamed: D75.A, PWR_LED7.1
unnamed: D76.A, ON_LED7.1
unnamed: D76.C, R55.2
unnamed: D80.C, J31.11
unnamed: D79.C, J31.12
unnamed: C99.1, D77.C, D78.C, R53.2, U16.8
RI/CTS2_1: TP23.1, U3.7
RI/CTS2_2: TP40.1, U5.7
RI/CTS2_3: TP57.1, U7.7
RI/CTS2_4: TP74.1, U9.7
RI/CTS2_5: TP91.1, U11.7
RI/CTS2_6: TP108.1, U13.7
RI/CTS2_7: TP125.1, U15.7
RI/CTS2_18: TP6.1, U1.7
RTS_1: IC2.6, U3.10
RTS_2: IC2.11, J7.10, R14.2
RTS_3: IC5.6, U5.10
RTS_4: IC5.11, J11.10, R21.2
RTS_5: IC7.6, U7.10
RTS_6: IC7.11, J15.10, R28.2
RTS_7: IC9.6, U9.10
RTS_8: IC9.11, J19.10, R35.2
RTS_9: IC11.6, U11.10
RTS_10: IC11.11, J23.10, R42.2
RTS_11: IC13.6, U13.10
RTS_12: IC13.11, J27.10, R49.2
RTS_13: IC15.6, U15.10
RTS_14: IC15.11, J31.10, R56.2
RTS_18: IC1.6, U1.10
RTS_33: IC1.11, J2.10, R7.2
RXD_1: IC2.3, U3.13
RXD_2: IC2.14, J7.7
RXD_3: IC5.3, U5.13
RXD_4: IC5.14, J11.7
RXD_5: IC7.3, U7.13
RXD_6: IC7.14, J15.7
RXD_7: IC9.3, U9.13
RXD_8: IC9.14, J19.7
RXD_9: IC11.3, U11.13
RXD_10: IC11.14, J23.7
RXD_11: IC13.3, U13.13
RXD_12: IC13.14, J27.7
RXD_13: IC15.3, U15.13
RXD_14: IC15.14, J31.7
RXD_18: IC1.3, U1.13
RXD_33: IC1.14, J2.7
SCL_1: TP19.1, U3.27
SCL_2: TP36.1, U5.27
SCL_3: TP53.1, U7.27
SCL_4: TP70.1, U9.27
SCL_5: TP87.1, U11.27
SCL_6: TP104.1, U13.27
SCL_7: TP121.1, U15.27
SCL_18: TP2.1, U1.27
SDA_1: TP18.1, U3.26
SDA_2: TP35.1, U5.26
SDA_3: TP52.1, U7.26
SDA_4: TP69.1, U9.26
SDA_5: TP86.1, U11.26
SDA_6: TP103.1, U13.26
SDA_7: TP120.1, U15.26
SDA_18: TP1.1, U1.26
SHLD: J4.SHLD1, J4.SHLD2, J4.SHLD3, J4.SHLD4, SHLD.2
SHLD1: J5.SHLD1, J5.SHLD2, J5.SHLD3, J5.SHLD4, SHLD1.2
SHLD2: J9.SHLD1, J9.SHLD2, J9.SHLD3, J9.SHLD4, SHLD2.2
SHLD3: J13.SHLD1, J13.SHLD2, J13.SHLD3, J13.SHLD4, SHLD3.2
SHLD4: J17.SHLD1, J17.SHLD2, J17.SHLD3, J17.SHLD4, SHLD4.2
SHLD5: J21.SHLD1, J21.SHLD2, J21.SHLD3, J21.SHLD4, SHLD5.2
SHLD6: J25.SHLD1, J25.SHLD2, J25.SHLD3, J25.SHLD4, SHLD6.2
SHLD7: J29.SHLD1, J29.SHLD2, J29.SHLD3, J29.SHLD4, SHLD7.2
SIM_CLK: C2.1, D4.4, J1.C3, U1.38
SIM_CLK1: C16.1, D14.4, J6.C3, U3.38
SIM_CLK2: C29.1, D24.4, J10.C3, U5.38
SIM_CLK3: C42.1, D34.4, J14.C3, U7.38
SIM_CLK4: C55.1, D44.4, J18.C3, U9.38
SIM_CLK5: C68.1, D54.4, J22.C3, U11.38
SIM_CLK6: C81.1, D64.4, J26.C3, U13.38
SIM_CLK7: C94.1, D74.4, J30.C3, U15.38
SIM_DET: J1.CD, R1.1, U1.42
SIM_DET1: J6.CD, R10.1, U3.42
SIM_DET2: J10.CD, R17.1, U5.42
SIM_DET3: J14.CD, R24.1, U7.42
SIM_DET4: J18.CD, R31.1, U9.42
SIM_DET5: J22.CD, R38.1, U11.42
SIM_DET6: J26.CD, R45.1, U13.42
SIM_DET7: J30.CD, R52.1, U15.42
SIM_IO: C3.1, D4.6, J1.C7, U1.39
SIM_IO1: C15.1, D14.6, J6.C7, U3.39
SIM_IO2: C28.1, D24.6, J10.C7, U5.39
SIM_IO3: C41.1, D34.6, J14.C7, U7.39
SIM_IO4: C54.1, D44.6, J18.C7, U9.39
SIM_IO5: C67.1, D54.6, J22.C7, U11.39
SIM_IO6: C80.1, D64.6, J26.C7, U13.39
SIM_IO7: C93.1, D74.6, J30.C7, U15.39
SIM_RST: C1.1, D4.3, J1.C2, U1.40
SIM_RST1: C14.1, D14.3, J6.C2, U3.40
SIM_RST2: C27.1, D24.3, J10.C2, U5.40
SIM_RST3: C40.1, D34.3, J14.C2, U7.40
SIM_RST4: C53.1, D44.3, J18.C2, U9.40
SIM_RST5: C66.1, D54.3, J22.C2, U11.40
SIM_RST6: C79.1, D64.3, J26.C2, U13.40
SIM_RST7: C92.1, D74.3, J30.C2, U15.40
TXD_1: IC2.4, U3.12
TXD_2: IC2.13, J7.8
TXD_3: IC5.4, U5.12
TXD_4: IC5.13, J11.8
TXD_5: IC7.4, U7.12
TXD_6: IC7.13, J15.8
TXD_7: IC9.4, U9.12
TXD_8: IC9.13, J19.8
TXD_9: IC11.4, U11.12
TXD_10: IC11.13, J23.8
TXD_11: IC13.4, U13.12
TXD_12: IC13.13, J27.8
TXD_13: IC15.4, U15.12
TXD_14: IC15.13, J31.8
TXD_18: IC1.4, U1.12
TXD_33: IC1.13, J2.8
USB_N: D1.6, U1.28
USB_N1: D11.6, U3.28
USB_N2: D21.6, U5.28
USB_N3: D31.6, U7.28
USB_N4: D41.6, U9.28
USB_N5: D51.6, U11.28
USB_N6: D61.6, U13.28
USB_N7: D71.6, U15.28
USB_P: D1.4, U1.29
USB_P1: D11.4, U3.29
USB_P2: D21.4, U5.29
USB_P3: D31.4, U7.29
USB_P4: D41.4, U9.29
USB_P5: D51.4, U11.29
USB_P6: D61.4, U13.29
USB_P7: D71.4, U15.29
VIN: D8.A, J3.2
VIN1: D18.A, J8.2
VIN2: D28.A, J12.2
VIN3: D38.A, J16.2
VIN4: D48.A, J20.2
VIN5: D58.A, J24.2
VIN6: D68.A, J28.2
VIN7: D78.A, J32.2
VSIM: C4.1, C5.1, D4.1, J1.C1, U1.41
VSIM1: C17.1, C18.1, D14.1, J6.C1, U3.41
VSIM2: C30.1, C31.1, D24.1, J10.C1, U5.41
VSIM3: C43.1, C44.1, D34.1, J14.C1, U7.41
VSIM4: C56.1, C57.1, D44.1, J18.C1, U9.41
VSIM5: C69.1, C70.1, D54.1, J22.C1, U11.41
VSIM6: C82.1, C83.1, D64.1, J26.C1, U13.41
VSIM7: C95.1, C96.1, D74.1, J30.C1, U15.41
V_USB: D1.5, F1.1, J4.VBUS1, J4.VBUS2, U1.17
V_USB1: D11.5, F2.1, J5.VBUS1, J5.VBUS2, U3.17
V_USB2: D21.5, F3.1, J9.VBUS1, J9.VBUS2, U5.17
V_USB3: D31.5, F4.1, J13.VBUS1, J13.VBUS2, U7.17
V_USB4: D41.5, F5.1, J17.VBUS1, J17.VBUS2, U9.17
V_USB5: D51.5, F6.1, J21.VBUS1, J21.VBUS2, U11.17
V_USB6: D61.5, F7.1, J25.VBUS1, J25.VBUS2, U13.17
V_USB7: D71.5, F8.1, J29.VBUS1, J29.VBUS2, U15.17

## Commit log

2023-09-07 Add datasheet and integration manual
2023-09-07 Add initial schematic and layout
2023-09-08 End of day commit
    Extend board length
    Start adding passives
    Plan more routing
2023-09-11 Finish initial layout of v01
    Change UART2, I2C, and GPIO pins to only be accessible via test points
    Shrink board length to 3" again
    Set initial header pinouts
    Add decoupling capacitors
    Route all air wires
    Route USB and RF traces with proper impedance
2023-09-13 Design review updates
    Extend board length to 3.25"
    Remove u.FL connectors
    Rename UART pins to match u-blox naming
    Add Reset and PWR_ON buttons and header pads
    Add power LEDs
    Add fiducials
2023-09-14 Design Review Updates
    Add diodes to PWR_ON and RESET PTH pads to protect against higher voltage inputs
    Move R7 to other side of level shifter
    Add SIM card outline to bottom silk
    Prevent bridging between pads of level shifters
    Remove 5V PTH pad
    Add dueling diodes to VREG input
2023-09-14 Design Review Updates
    Add note to silkscreen about voltage level for PTH pads and test points
    Move PWR LED via away from USB trace
    Adjust measure for SIM card
    Add ordering instructions
2023-09-15 Design review updates
    Update Eagle libraries to fix vector fonts for some symbols
    Add GND vias near SIM holder pads
    Add max input voltage for VREG
    Straighten USB trace near connector (N$10)
    Fix trace on ANT1 ESD pad
2023-09-15 Add v01 production files
2023-09-15 Clean up design
    Increase frame to ledger size
    Arrange test points in schematic to match physical layout
    Add impedance calculations to schematic
    Update LED VALUE attributes with color in schematic
    Add silkscreen labels to test points
    Decrease font size of top buzzard labels to make tails more visible
2023-10-17 v10 updates
    Bump version number to v10
    Add AT Commands Manual
    Add Application Development App Note
    Add Audio App Note
    Fix text in Antenna Connectors section to be "Coplanar Waveguide Calculation"
    Reposition D7 and D8 so text is horizontal
2023-10-17 Add v10 Panel
2023-10-17 Change SMA connector PROD_ID
2023-11-09 Initial Docs commit
    Initial docs commit to add background files & first draft of guide.
2023-11-15 v11 - Label SMA connectors in silkscreen
2023-11-29 Update docs
    Documentation content update.
2023-12-07 Docs Update (m-center)
    Updating documentation with m-center section & relevant screenshots.
2023-12-12 Docs Update
    Initial commit to update software sections for m-center & Arduino library.
2023-12-15 Swap 100uF capacitor for new alternative
2023-12-20 Docs update
    Updating docs with board files & Arduino/m-center sections.
2023-12-21 Docs Update
    Photo dump & minor tweaks/edits.
2024-01-02 Update README.md
    Update readme.
2024-01-04 Update introduction.md
    Commenting out video HTML until it's released.
2024-01-04 Docs update
    Adding code snippets and fixing intro video link.
2024-01-04 Update Docs
    Small fixes and video embed.
2024-01-04 Photo Update
    Updating with cropped photos.
2024-01-11 Add breadboard phone example code
2024-01-31 Update README.md
    Fixing typos.
2024-02-06 Docs Update
    Updating docs to switch from "Hard Copy" to "Print View"
2024-02-06 Deployed c8419e8 with MkDocs version: 1.5.3
2024-10-25 Update mkdocs.yml
    Analytics update.
2024-10-25 Deployed 68ef3ea with MkDocs version: 1.6.1
